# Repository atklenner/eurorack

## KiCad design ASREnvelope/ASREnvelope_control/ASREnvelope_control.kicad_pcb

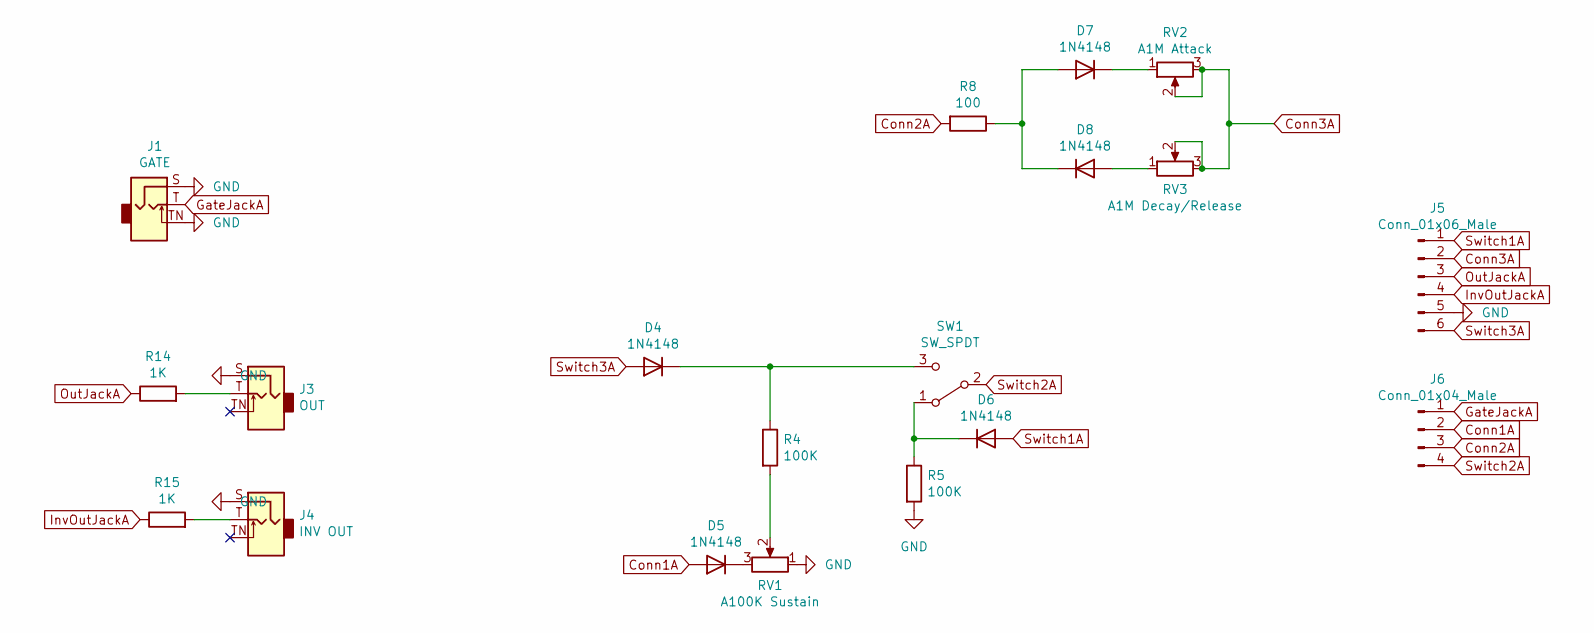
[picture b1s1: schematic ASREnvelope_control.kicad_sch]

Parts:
D4, D5, D6, D7, D8: 1N4148; D_DO-35_SOD27_P7.62mm_Horizontal
J1: GATE; Jack_3.5mm_QingPu_WQP-PJ398SM_Vertical
J3: OUT; Jack_3.5mm_QingPu_WQP-PJ398SM_Vertical
J4: INV OUT; Jack_3.5mm_QingPu_WQP-PJ398SM_Vertical
J5: Conn_01x06_Male; PinHeader_1x06_P2.54mm_Vertical
J6: Conn_01x04_Male; PinHeader_1x04_P2.54mm_Vertical
R4, R5: 100K; R_Axial_DIN0207_L6.3mm_D2.5mm_P7.62mm_Horizontal
R8: 100; R_Axial_DIN0207_L6.3mm_D2.5mm_P7.62mm_Horizontal
R14, R15: 1K; R_Axial_DIN0207_L6.3mm_D2.5mm_P7.62mm_Horizontal
RV1: A100K Sustain; Alpha9mmPot
RV2: A1M Attack; Alpha9mmPot
RV3: A1M Decay/Release; Alpha9mmPot
SW1: SW_SPDT; SPDT toggle on-off-on

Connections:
Conn1A: D5.2 (A), J6.2
Conn2A: J6.3, R8.2
Conn3A: J5.2, RV2.2, RV2.3, RV3.2, RV3.3
GND: J1.S, J1.TN, J3.S, J4.S, J5.5, R5.2, RV1.1
GateJackA: J1.T, J6.1
InvOutJackA: J5.4, R15.1
unnamed: D4.1 (K), R4.1, SW1.3 (C)
unnamed: D5.1 (K), RV1.3
unnamed: D6.1 (K), R5.1, SW1.1 (A)
unnamed: D7.1 (K), RV2.1
unnamed: D7.2 (A), D8.1 (K), R8.1
unnamed: D8.2 (A), RV3.1
unnamed: J3.T, R14.2
unnamed: J4.T, R15.2
unnamed: R4.2, RV1.2
OutJackA: J5.3, R14.1
Switch1A: D6.2 (A), J5.1
Switch2A: J6.4, SW1.2 (B)
Switch3A: D4.2 (A), J5.6

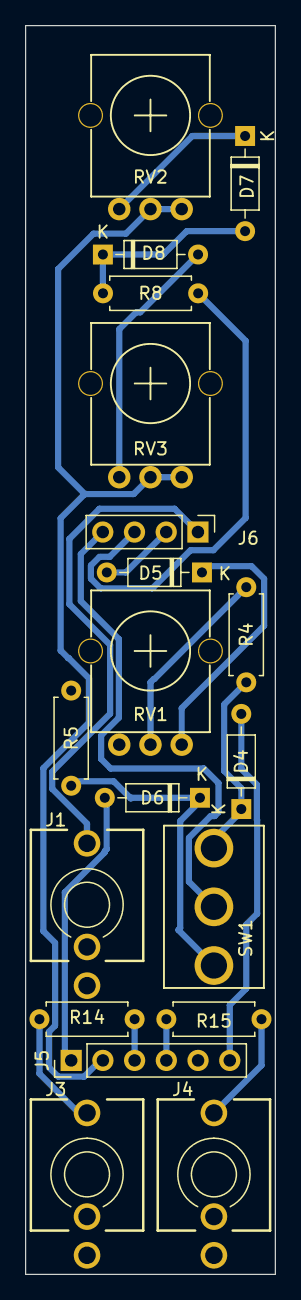
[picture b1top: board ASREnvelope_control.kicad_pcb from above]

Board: 2 copper layers, 20.0 x 100.0 mm, 19 parts (0 on the bottom side), 19 nets.

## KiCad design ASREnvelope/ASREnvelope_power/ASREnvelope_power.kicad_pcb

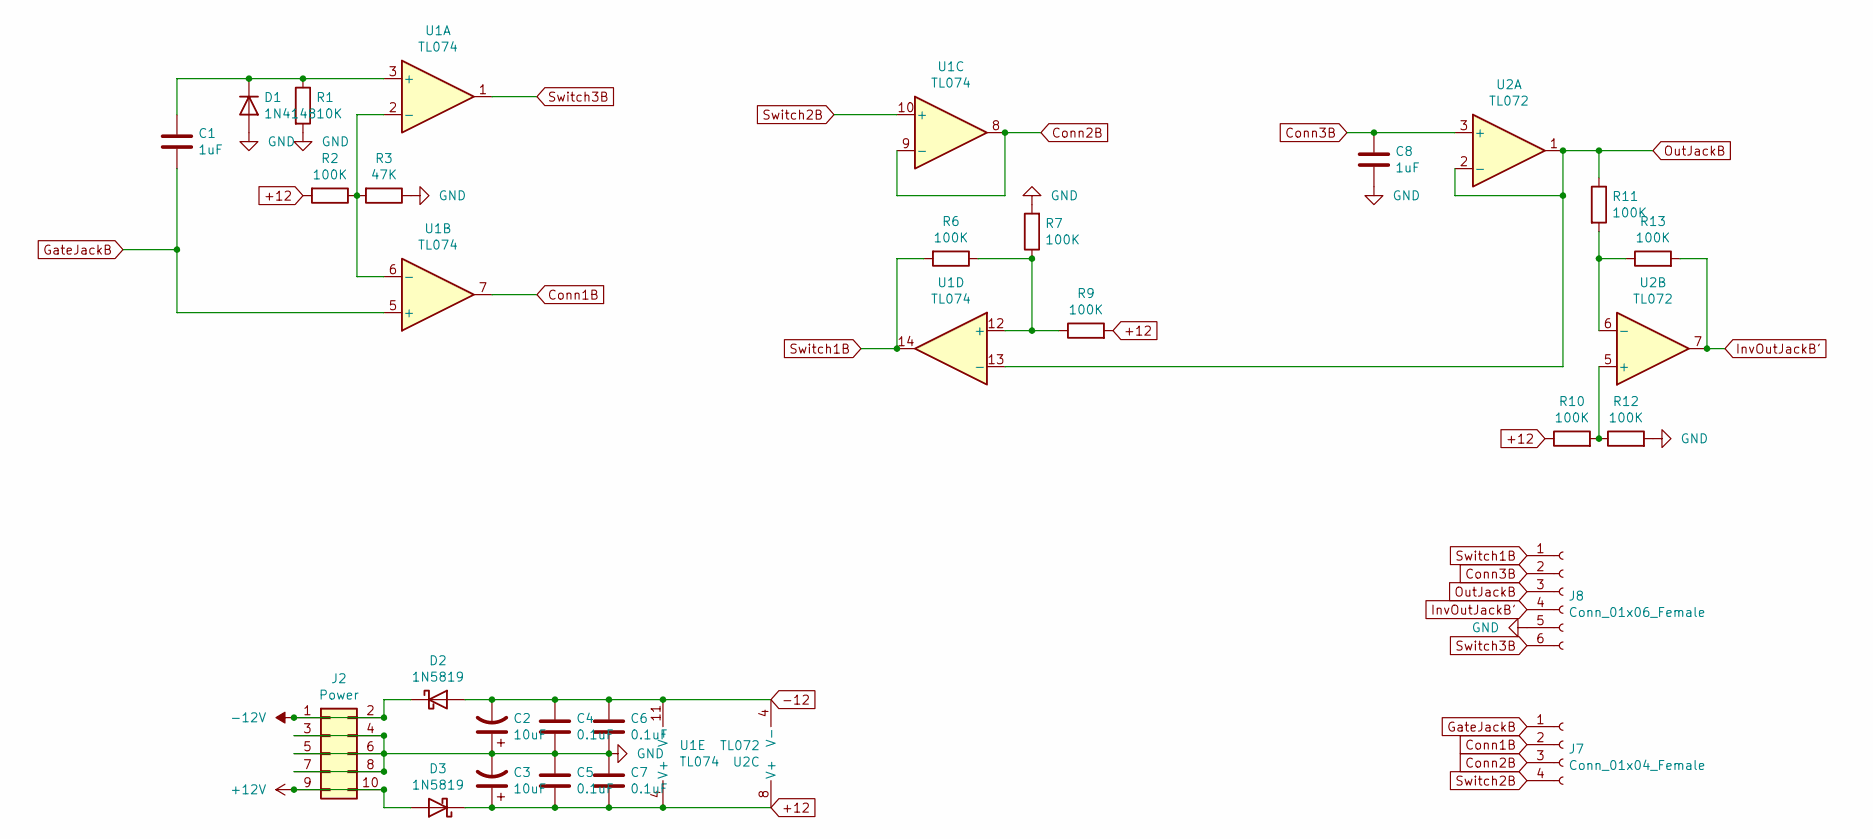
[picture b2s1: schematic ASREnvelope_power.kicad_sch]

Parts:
C1, C8: 1uF; C_Disc_D3.0mm_W1.6mm_P2.50mm
C2, C3: 10uF; CP_Radial_D5.0mm_P2.50mm
C4, C5, C6, C7: 0.1uF; C_Disc_D11.0mm_W5.0mm_P7.50mm
D1: 1N4148; D_DO-35_SOD27_P7.62mm_Horizontal
D2, D3: 1N5819; D_DO-41_SOD81_P7.62mm_Horizontal
J2: Power; PinHeader_2x05_P2.54mm_Horizontal
J7: Conn_01x04_Female; PinSocket_1x04_P2.54mm_Vertical
J8: Conn_01x06_Female; PinSocket_1x06_P2.54mm_Vertical
R1: 10K; R_Axial_DIN0207_L6.3mm_D2.5mm_P7.62mm_Horizontal
R2, R6, R7, R9, R10, R11, R12, R13: 100K; R_Axial_DIN0207_L6.3mm_D2.5mm_P7.62mm_Horizontal
R3: 47K; R_Axial_DIN0207_L6.3mm_D2.5mm_P7.62mm_Horizontal
U1: TL074; DIP-14_W7.62mm_Socket_LongPads
U2: TL072; DIP-8_W7.62mm_Socket_LongPads

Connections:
+12: C3.1, C5.2, C7.2, D3.1 (K), R2.2, R9.2, R10.1, U1.4 (V+), U2.8 (V+)
+12V: D3.2 (A), J2.9, J2.10
-12: C2.2, C4.1, C6.1, D2.2 (A), U1.11 (V-), U2.4 (V-)
-12V: D2.1 (K), J2.1, J2.2
Conn1B: J7.2, U1.7
Conn2B: J7.3, U1.8, U1.9 (-)
Conn3B: C8.1, J8.2, U2.3 (+)
GND: C2.1, C3.2, C4.2, C5.1, C6.2, C7.1, C8.2, D1.2 (A), J2.3, J2.4, J2.5, J2.6, J2.7, J2.8, J8.5, R1.2, R3.1, R7.2, R12.2
GateJackB: C1.2, J7.1, U1.5 (+)
InvOutJackB': J8.4, R13.2, U2.7
unnamed: C1.1, D1.1 (K), R1.1, U1.3 (+)
unnamed: R2.1, R3.2, U1.2 (-), U1.6 (-)
unnamed: R6.1, R7.1, R9.1, U1.12 (+)
unnamed: R10.2, R12.1, U2.5 (+)
unnamed: R11.2, R13.1, U2.6 (-)
OutJackB: J8.3, R11.1, U1.13 (-), U2.1, U2.2 (-)
Switch1B: J8.1, R6.2, U1.14
Switch2B: J7.4, U1.10 (+)
Switch3B: J8.6, U1.1

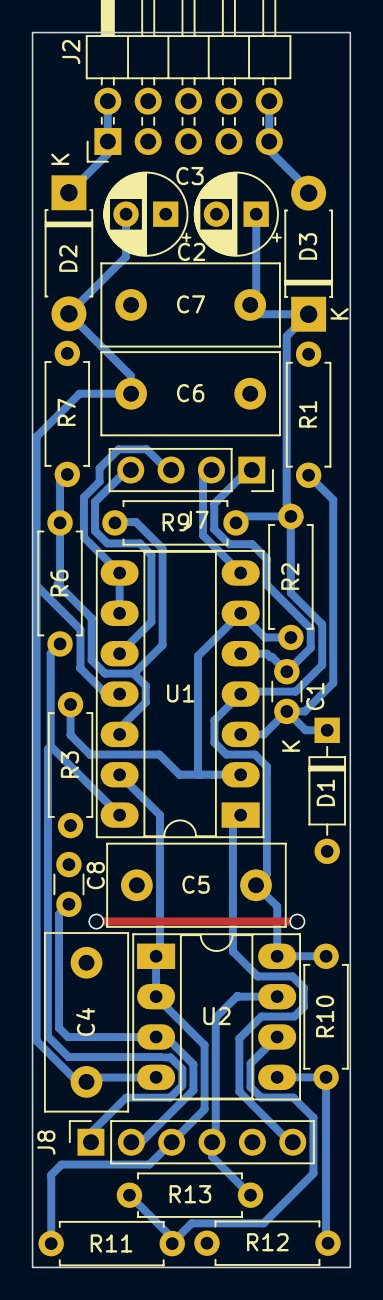
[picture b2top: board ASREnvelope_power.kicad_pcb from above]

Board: 2 copper layers, 20.0 x 77.7 mm, 26 parts (0 on the bottom side), 19 nets.

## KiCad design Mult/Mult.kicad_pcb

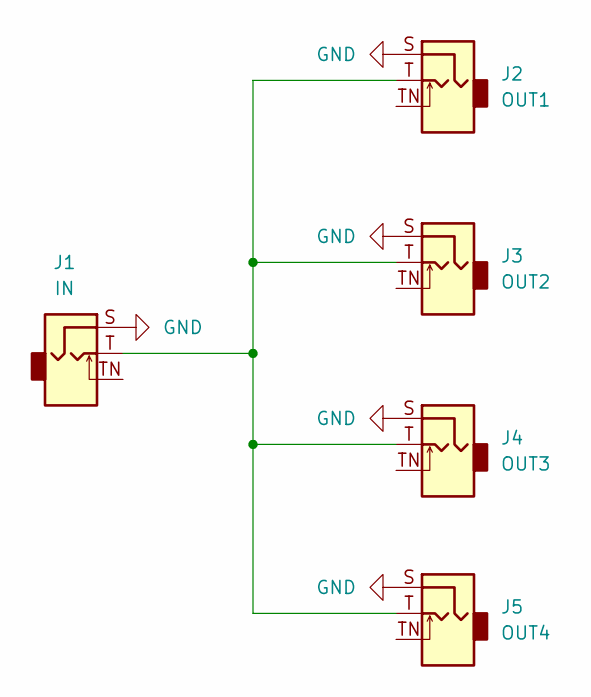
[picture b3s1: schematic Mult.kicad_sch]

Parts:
J1: IN; Jack_3.5mm_QingPu_WQP-PJ398SM_Vertical
J2: OUT1; Jack_3.5mm_QingPu_WQP-PJ398SM_Vertical
J3: OUT2; Jack_3.5mm_QingPu_WQP-PJ398SM_Vertical
J4: OUT3; Jack_3.5mm_QingPu_WQP-PJ398SM_Vertical
J5: OUT4; Jack_3.5mm_QingPu_WQP-PJ398SM_Vertical

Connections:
GND: J1.S, J2.S, J3.S, J4.S, J5.S
unnamed: J1.T, J2.T, J3.T, J4.T, J5.T

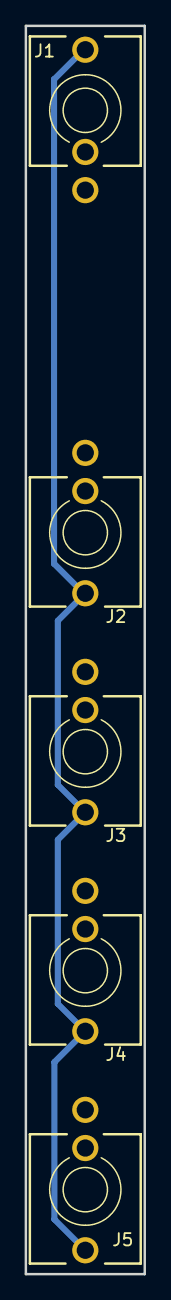
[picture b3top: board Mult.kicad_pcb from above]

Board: 2 copper layers, 9.7 x 101.3 mm, 5 parts (0 on the bottom side), 2 nets.

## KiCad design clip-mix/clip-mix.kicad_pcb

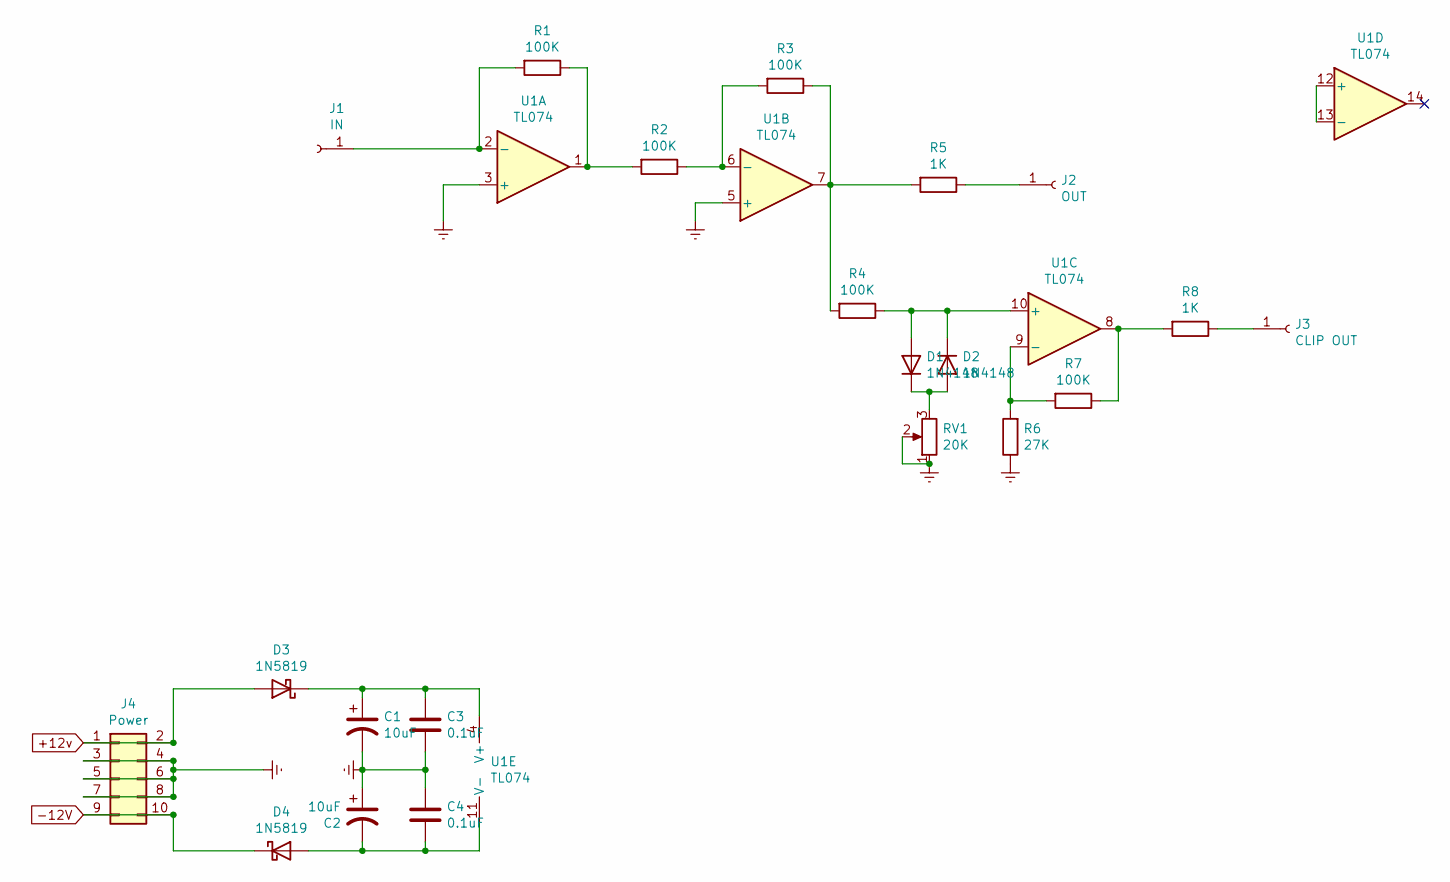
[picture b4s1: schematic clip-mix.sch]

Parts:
C1, C2: 10uF; CP_Radial_D5.0mm_P2.00mm
C3, C4: 0.1uF; C_Disc_D7.5mm_W5.0mm_P7.50mm
D1, D2: 1N4148; D_T-1_P5.08mm_Horizontal
D3, D4: 1N5819; D_T-1_P5.08mm_Horizontal
J1: IN; SolderWire-0.5sqmm_1x01_D0.9mm_OD2.3mm
J2: OUT; SolderWire-0.5sqmm_1x01_D0.9mm_OD2.3mm
J3: CLIP OUT; SolderWire-0.5sqmm_1x01_D0.9mm_OD2.3mm
J4: Power; PinHeader_2x05_P2.54mm_Vertical
R1, R2, R3, R4, R7: 100K; R_Axial_DIN0204_L3.6mm_D1.6mm_P7.62mm_Horizontal
R5, R8: 1K; R_Axial_DIN0204_L3.6mm_D1.6mm_P7.62mm_Horizontal
R6: 27K; R_Axial_DIN0204_L3.6mm_D1.6mm_P7.62mm_Horizontal
RV1: 20K; Potentiometer_Bourns_3296W_Vertical
U1: TL074; DIP-14_W7.62mm_Socket

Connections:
+12v: D3.2 (A), J4.1, J4.2
-12V: D4.1 (K), J4.9, J4.10
Earth: C1.2, C2.1, C3.2, C4.1, J4.3, J4.4, J4.5, J4.6, J4.7, J4.8, R6.1, RV1.1, RV1.2, U1.3 (+), U1.5 (+)
unnamed: C1.1, C3.1, D3.1 (K), U1.4 (V+)
unnamed: C2.2, C4.2, D4.2 (A), U1.11 (V-)
unnamed: D1.1 (K), D2.2 (A), RV1.3
unnamed: D1.2 (A), D2.1 (K), R4.1, U1.10 (+)
unnamed: J1.1, R1.2, U1.2 (-)
unnamed: J2.1, R5.1
unnamed: J3.1, R8.1
unnamed: R1.1, R2.2, U1.1
unnamed: R2.1, R3.2, U1.6 (-)
unnamed: R3.1, R4.2, R5.2, U1.7
unnamed: R6.2, R7.2, U1.9 (-)
unnamed: R7.1, R8.2, U1.8
unnamed: U1.12 (+), U1.13 (-)

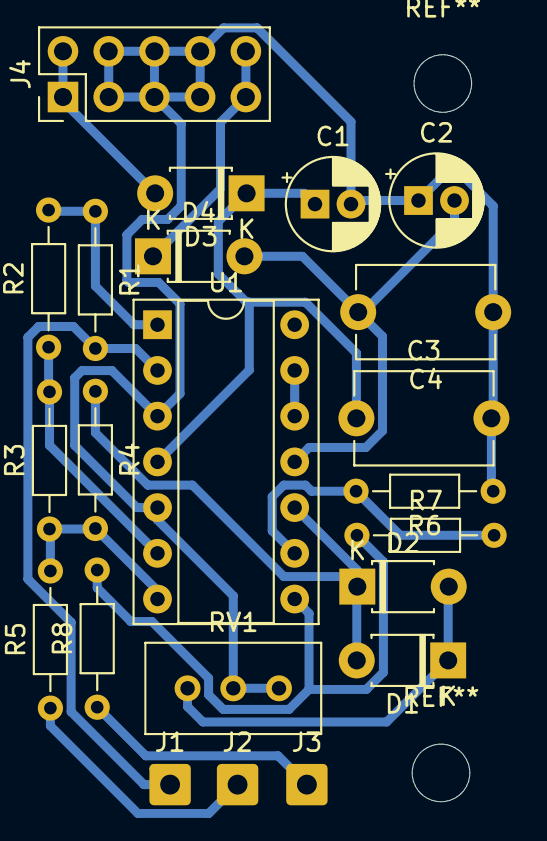
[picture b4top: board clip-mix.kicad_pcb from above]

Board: 2 copper layers, 22 parts (0 on the bottom side), 16 nets.

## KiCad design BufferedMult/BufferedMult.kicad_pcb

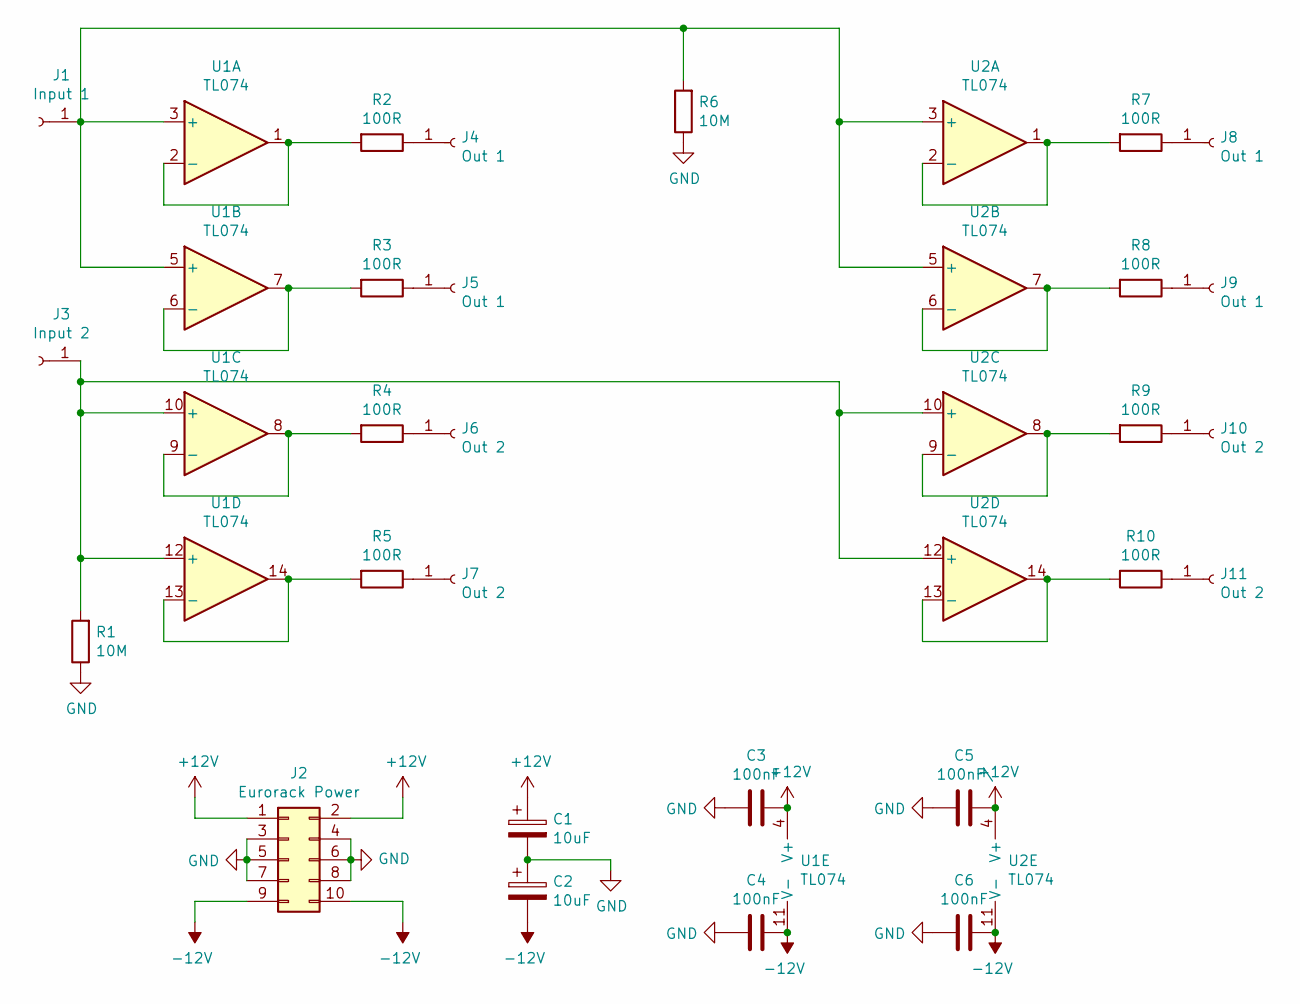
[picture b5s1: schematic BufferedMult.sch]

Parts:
C1, C2: 10uF; C_Radial_D5.0mm_H11.0mm_P2.00mm
C3, C4, C6: 100nF; C_Rect_L10.3mm_W5.0mm_P7.50mm_MKS4
C5: 100nF\\; C_Rect_L10.3mm_W5.0mm_P7.50mm_MKS4
J1: Input 1; PinHeader_1x01_P2.54mm_Vertical
J2: Eurorack Power; PinHeader_2x05_P2.54mm_Vertical
J3: Input 2; PinHeader_1x01_P2.54mm_Vertical
J4, J5, J8, J9: Out 1; PinHeader_1x01_P2.54mm_Vertical
J6, J7, J10, J11: Out 2; PinHeader_1x01_P2.54mm_Vertical
R1, R6: 10M; R_Axial_DIN0207_L6.3mm_D2.5mm_P2.54mm_Vertical
R2, R3, R4, R5, R7, R8, R9, R10: 100R; R_Axial_DIN0207_L6.3mm_D2.5mm_P2.54mm_Vertical
U1, U2: TL074; DIP-14_W7.62mm_Socket

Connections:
+12V: C1.1, C3.1, C5.1, J2.1, J2.2, U1.4 (V+), U2.4 (V+)
-12V: C2.2, C4.1, C6.1, J2.9, J2.10, U1.11 (V-), U2.11 (V-)
GND: C1.2, C2.1, C3.2, C4.2, C5.2, C6.2, J2.3, J2.4, J2.5, J2.6, J2.7, J2.8, R1.1, R6.1
unnamed: J1.1, R6.2, U1.3 (+), U1.5 (+), U2.3 (+), U2.5 (+)
unnamed: J3.1, R1.2, U1.10 (+), U1.12 (+), U2.10 (+), U2.12 (+)
unnamed: J4.1, R2.1
unnamed: J5.1, R3.1
unnamed: J6.1, R4.1
unnamed: J7.1, R5.1
unnamed: J8.1, R7.1
unnamed: J9.1, R8.1
unnamed: J10.1, R9.1
unnamed: J11.1, R10.1
unnamed: R2.2, U1.1, U1.2 (-)
unnamed: R3.2, U1.6 (-), U1.7
unnamed: R4.2, U1.8, U1.9 (-)
unnamed: R5.2, U1.13 (-), U1.14
unnamed: R7.2, U2.1, U2.2 (-)
unnamed: R8.2, U2.6 (-), U2.7
unnamed: R9.2, U2.8, U2.9 (-)
unnamed: R10.2, U2.13 (-), U2.14

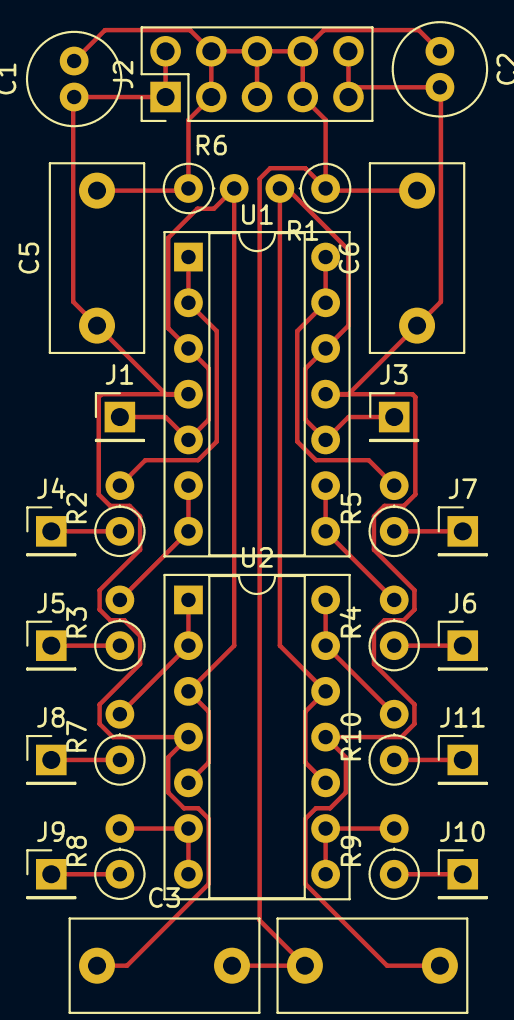
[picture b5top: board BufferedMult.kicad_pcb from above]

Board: 2 copper layers, 29 parts (0 on the bottom side), 21 nets.

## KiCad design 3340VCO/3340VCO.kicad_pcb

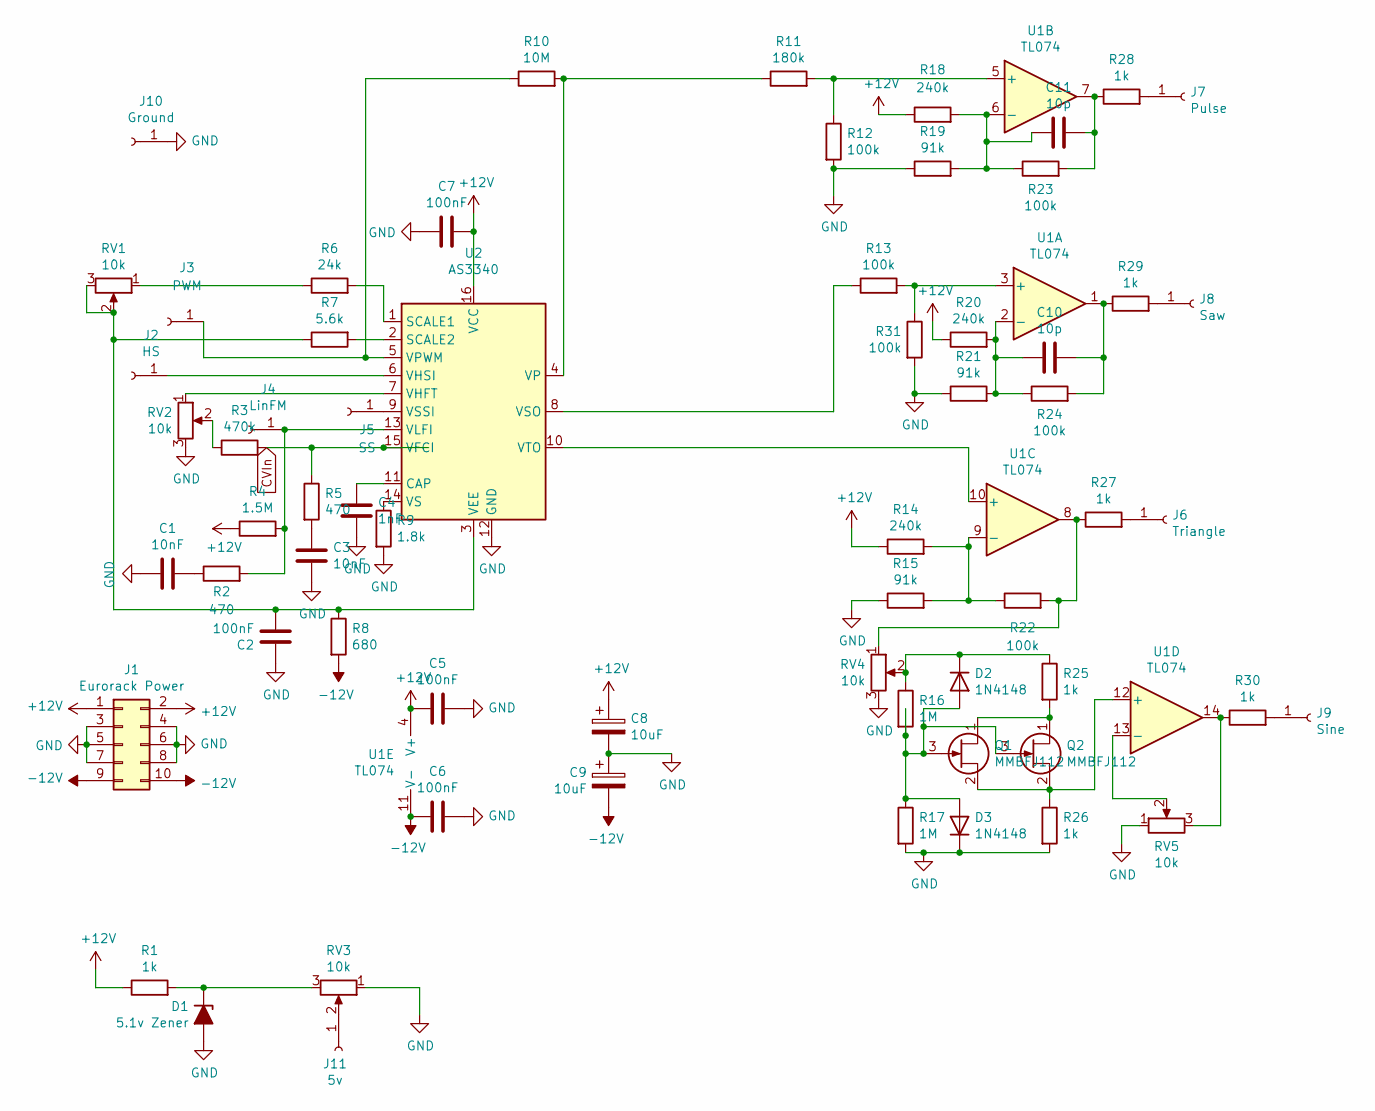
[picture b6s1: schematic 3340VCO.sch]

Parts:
C1, C3: 10nF; C_Disc_D5.0mm_W2.5mm_P2.50mm
C2, C5, C6, C7: 100nF; C_Disc_D10.5mm_W5.0mm_P7.50mm
C4: 1nF; C_Disc_D5.0mm_W2.5mm_P2.50mm
C8, C9: 10uF; CP_Radial_D5.0mm_P2.50mm
C10, C11: 10p; C_Disc_D3.8mm_W2.6mm_P2.50mm
D1: 5.1v Zener; D_DO-35_SOD27_P2.54mm_Vertical_AnodeUp
D2, D3: 1N4148; D_DO-35_SOD27_P2.54mm_Vertical_AnodeUp
J1: Eurorack Power; PinHeader_2x05_P2.54mm_Vertical
J2: HS; PinHeader_1x01_P2.54mm_Vertical
J3: PWM; PinHeader_1x01_P2.54mm_Vertical
J4: LinFM; PinHeader_1x01_P2.54mm_Vertical
J5: SS; PinHeader_1x01_P2.54mm_Vertical
J6: Triangle; PinHeader_1x01_P2.54mm_Vertical
J7: Pulse; PinHeader_1x01_P2.54mm_Vertical
J8: Saw; PinHeader_1x01_P2.54mm_Vertical
J9: Sine; PinHeader_1x01_P2.54mm_Vertical
J10: Ground; PinHeader_1x01_P2.54mm_Vertical
J11: 5v; PinHeader_1x01_P2.54mm_Vertical
Q1, Q2: MMBFJ112; SOT-23
R1, R25, R26, R27, R28, R29, R30: 1k; R_Axial_DIN0207_L6.3mm_D2.5mm_P2.54mm_Vertical
R2, R5: 470; R_Axial_DIN0207_L6.3mm_D2.5mm_P2.54mm_Vertical
R3: 470k; R_Axial_DIN0207_L6.3mm_D2.5mm_P2.54mm_Vertical
R4: 1.5M; R_Axial_DIN0207_L6.3mm_D2.5mm_P2.54mm_Vertical
R6: 24k; R_Axial_DIN0207_L6.3mm_D2.5mm_P2.54mm_Vertical
R7: 5.6k; R_Axial_DIN0207_L6.3mm_D2.5mm_P2.54mm_Vertical
R8: 680; R_Axial_DIN0207_L6.3mm_D2.5mm_P2.54mm_Vertical
R9: 1.8k; R_Axial_DIN0207_L6.3mm_D2.5mm_P2.54mm_Vertical
R10: 10M; R_Axial_DIN0207_L6.3mm_D2.5mm_P2.54mm_Vertical
R11: 180k; R_Axial_DIN0207_L6.3mm_D2.5mm_P2.54mm_Vertical
R12, R13, R22, R23, R24, R31: 100k; R_Axial_DIN0207_L6.3mm_D2.5mm_P2.54mm_Vertical
R14, R18, R20: 240k; R_Axial_DIN0207_L6.3mm_D2.5mm_P2.54mm_Vertical
R15, R19, R21: 91k; R_Axial_DIN0207_L6.3mm_D2.5mm_P2.54mm_Vertical
R16, R17: 1M; R_Axial_DIN0207_L6.3mm_D2.5mm_P2.54mm_Vertical
RV1, RV2, RV3, RV4, RV5: 10k; Potentiometer_Bourns_3296W_Vertical
U1: TL074; DIP-14_W7.62mm_Socket
U2: AS3340; DIP-16_W7.62mm_Socket

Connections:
+12V: C5.2, C7.2, C8.1, J1.1, J1.2, R1.1, R4.1, R14.1, R18.1, R20.1, U1.4 (V+), U2.16 (VCC)
-12V: C6.2, C9.2, J1.9, J1.10, R8.2, U1.11 (V-)
CVIn: R3.2, R5.1, U2.15 (VFCI)
GND: C1.2, C2.1, C3.1, C4.2, C5.1, C6.1, C7.1, C8.2, C9.1, D1.2 (A), D3.2 (K), J1.3, J1.4, J1.5, J1.6, J1.7, J1.8, J10.1, R9.2, R12.2, R15.1, R17.2, R19.1, R21.1, R26.2, R31.2, RV2.3, RV3.1, RV4.3, RV5.1, U2.12 (GND)
unnamed: C1.1, R2.1
unnamed: C2.2, R7.1, R8.1, RV1.2, RV1.3, U2.3 (VEE)
unnamed: C3.2, R5.2
unnamed: C4.1, U2.11 (CAP)
unnamed: C10.1, R20.2, R21.2, R24.1, U1.2 (-)
unnamed: C10.2, R24.2, R29.1, U1.1
unnamed: C11.1, R18.2, R19.2, R23.1, U1.6 (-)
unnamed: C11.2, R23.2, R28.1, U1.7
unnamed: D1.1 (K), R1.2, RV3.3
unnamed: D2.1 (A), D3.1 (A), Q1.3 (G), Q2.3 (G), R16.2, R17.1
unnamed: D2.2 (K), R16.1, R25.1, RV4.2
unnamed: J2.1, U2.6 (VHSI)
unnamed: J3.1, R10.1, U2.5 (VPWM)
unnamed: J4.1, R2.2, R4.2, U2.13 (VLFI)
unnamed: J5.1, U2.9 (VSSI)
unnamed: J6.1, R27.2
unnamed: J7.1, R28.2
unnamed: J8.1, R29.2
unnamed: J9.1, R30.2
unnamed: J11.1, RV3.2
unnamed: Q1.1 (D), Q2.1 (D), R25.2
unnamed: Q1.2 (S), Q2.2 (S), R26.1, U1.12 (+)
unnamed: R3.1, RV2.2
unnamed: R6.1, RV1.1
unnamed: R6.2, U2.1 (SCALE1)
unnamed: R7.2, U2.2 (SCALE2)
unnamed: R9.1, U2.14 (VS)
unnamed: R10.2, R11.1, U2.4 (VP)
unnamed: R11.2, R12.1, U1.5 (+)
unnamed: R13.1, U2.8 (VSO)
unnamed: R13.2, R31.1, U1.3 (+)
unnamed: R14.2, R15.2, R22.1, U1.9 (-)
unnamed: R22.2, R27.1, RV4.1, U1.8
unnamed: R30.1, RV5.3, U1.14
unnamed: RV2.1, U2.7 (VHFT)
unnamed: RV5.2, U1.13 (-)
unnamed: U1.10 (+), U2.10 (VTO)

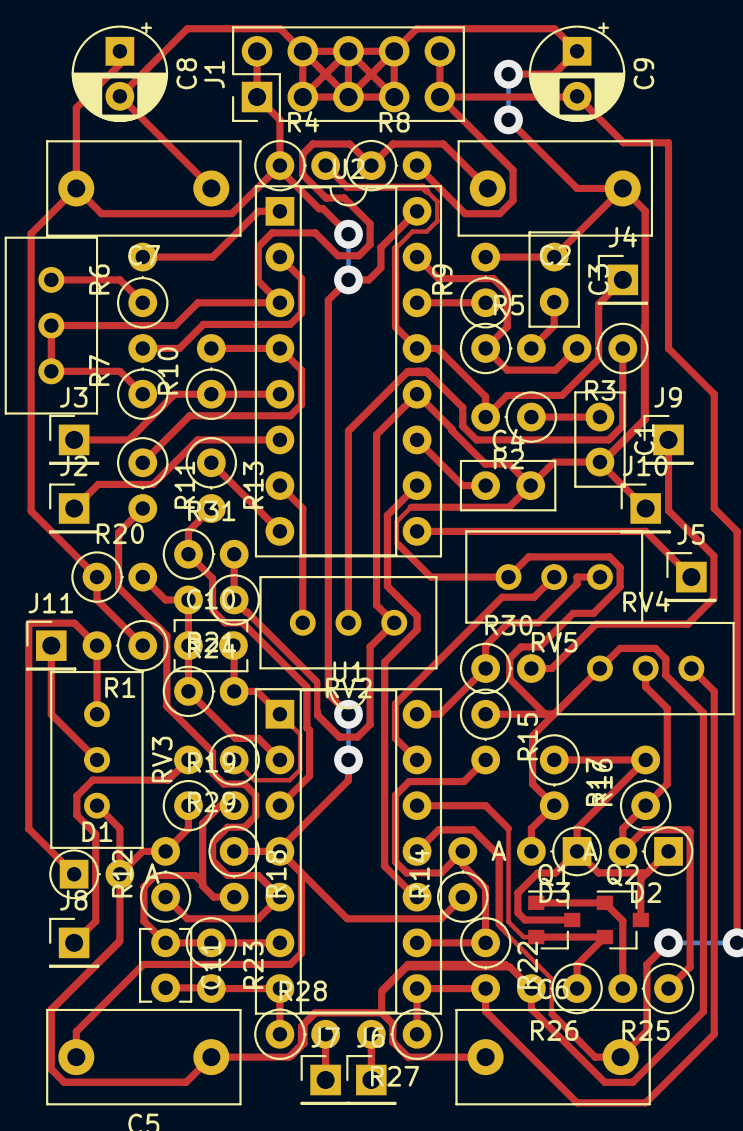
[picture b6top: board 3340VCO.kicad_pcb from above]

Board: 2 copper layers, 65 parts (0 on the bottom side), 41 nets.

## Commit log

2022-07-01 add designs
2022-07-04 work on test and clip mix
2022-07-04 start ASREnvelope
2022-07-06 fix file structure
2022-07-09 add footprints
2022-07-10 add through hole pot footprints
2022-07-12 move circuit to two boards
2022-07-27 add mult project
2022-08-01 add footprint model
2022-08-02 fix component step files
2022-08-05 rearrange a bunch of files
2022-08-06 add eurocad footprint library
2022-08-13 split envelope PCBs
2022-08-13 remove test project
2022-08-13 add misc folder
2022-08-13 reorganize old ASR project
2022-08-13 work on power traces
2022-08-13 fix control board connections
2022-08-14 finish control traces
2022-08-14 start on panel
2022-08-15 finish traces
2022-08-15 create gerbers
2022-08-15 add panel font
2022-08-15 finish panel model
2022-08-15 fix connector position
2022-08-15 generate gerbers
2022-08-17 fix errors
2022-08-20 start on VCA
